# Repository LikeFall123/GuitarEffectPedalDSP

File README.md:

BME Schönhhertz SEM Guitar Pedal Project

Addig digital effects to the sound of the guitar, by processing it with an STM32 microcontroller and a CODEC.

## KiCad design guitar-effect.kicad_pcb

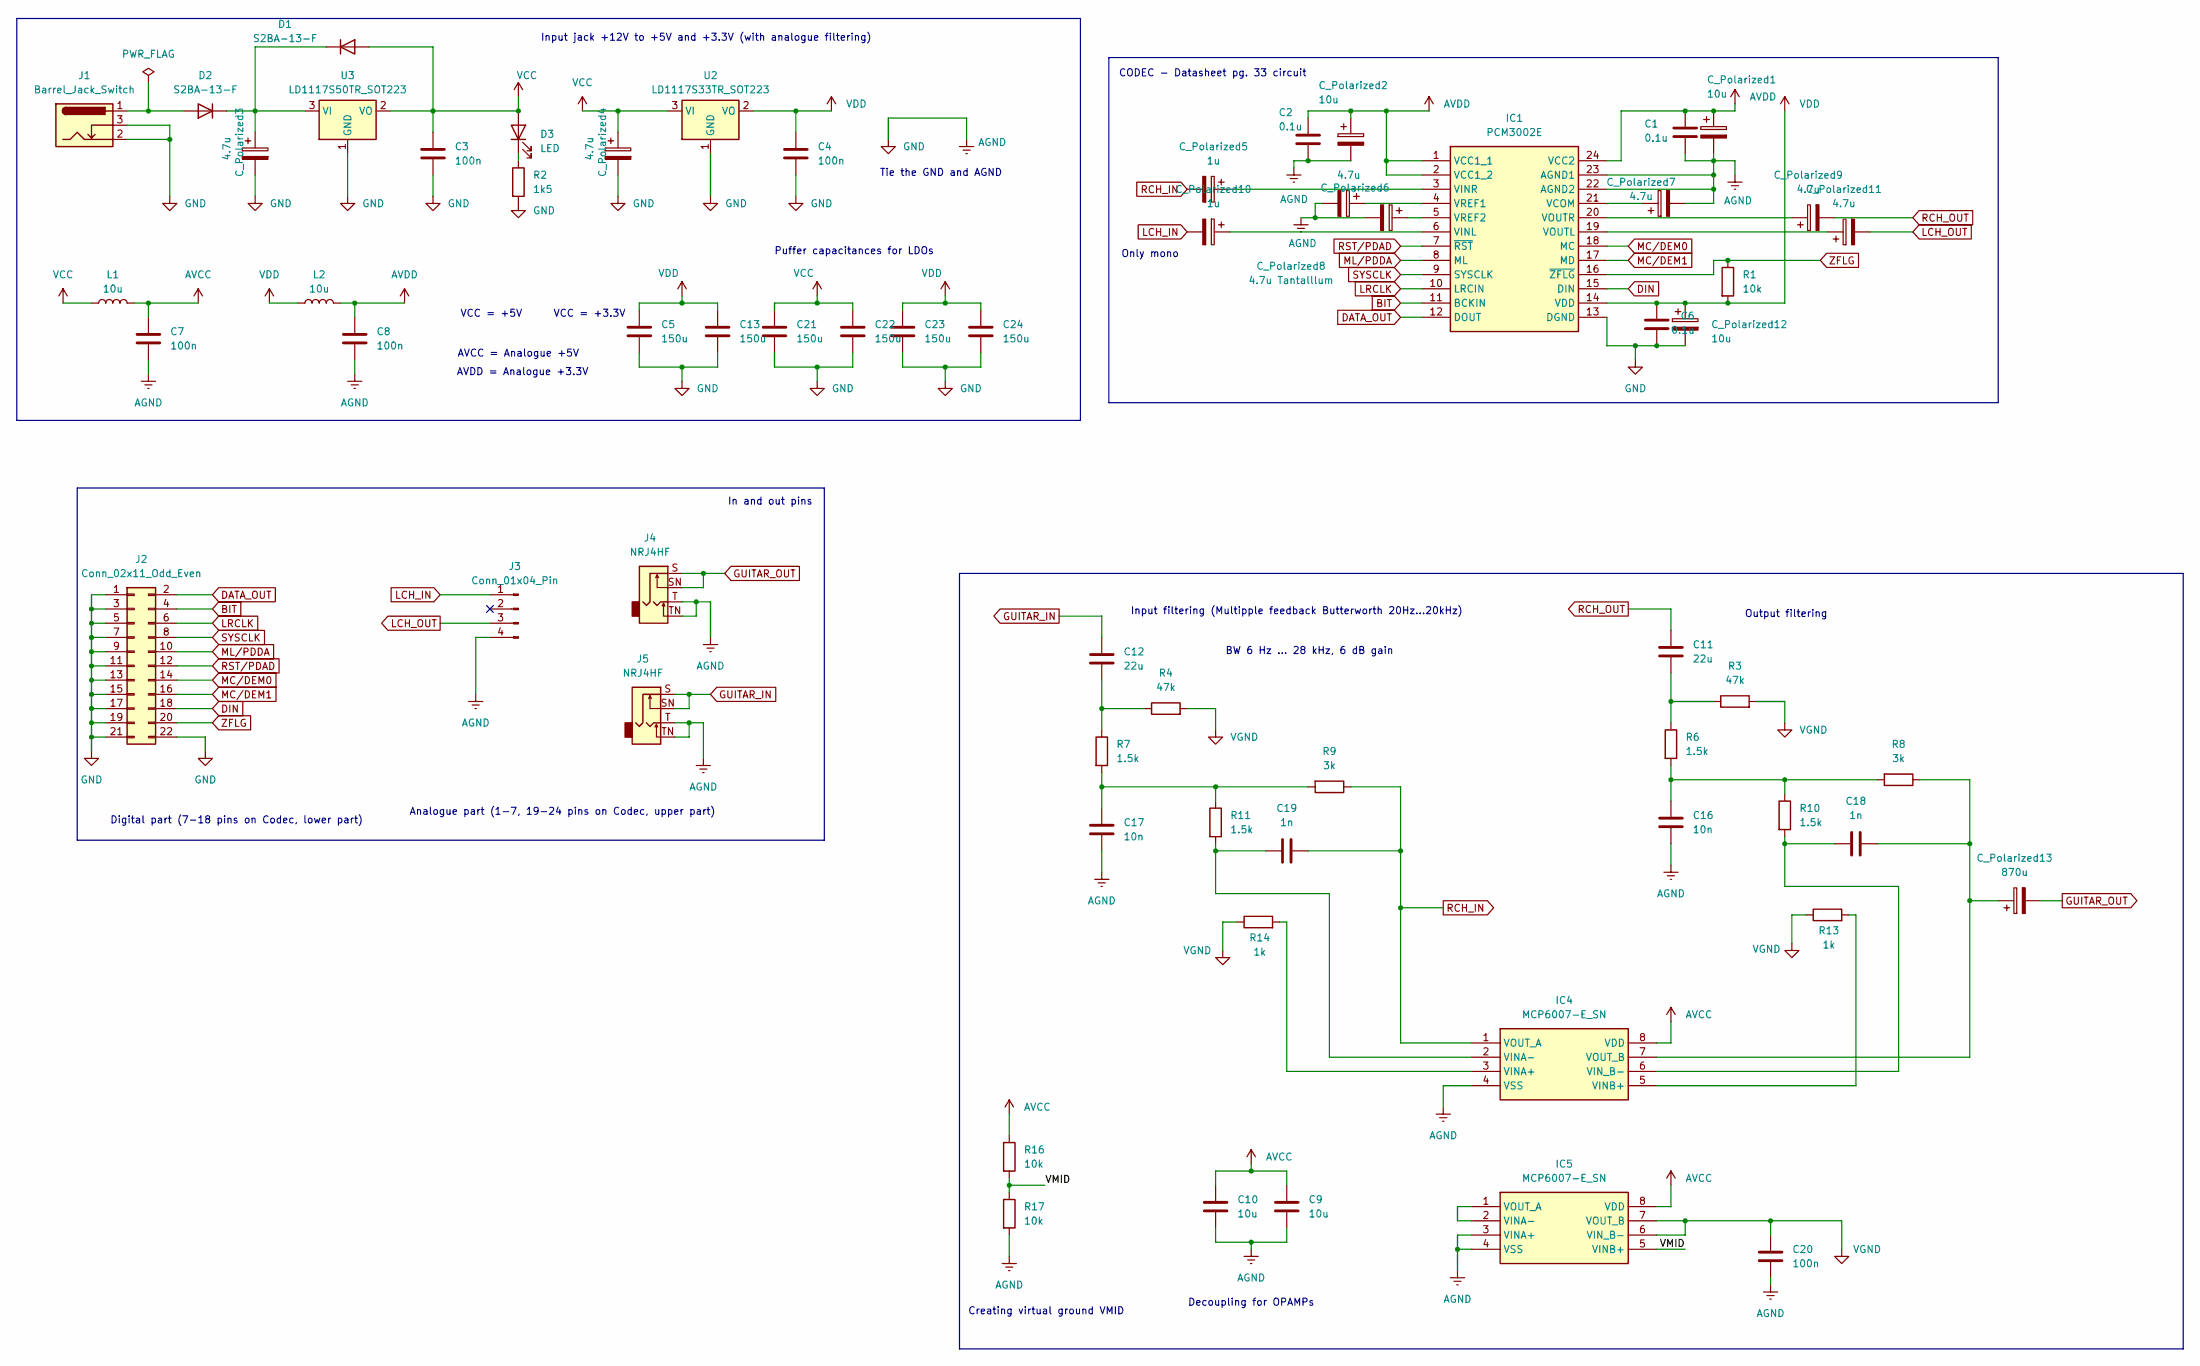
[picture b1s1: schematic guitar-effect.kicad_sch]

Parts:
C1, C2, C6: 0.1u; C_0805_2012Metric
C3, C4, C7, C8, C20: 100n; C_0805_2012Metric
C5, C13, C21, C22, C23, C24: 150u; C_1206_3216Metric
C9, C10: 10u; C_1206_3216Metric
C11, C12: 22u; C_0805_2012Metric
C16, C17: 10n; C_0805_2012Metric
C18, C19: 1n; C_0805_2012Metric
C_Polarized1, C_Polarized2, C_Polarized12: 10u; CP_Radial_D4.0mm_P1.50mm
C_Polarized3, C_Polarized4, C_Polarized6, C_Polarized7, C_Polarized9, C_Polarized11: 4.7u; CP_Radial_D4.0mm_P1.50mm
C_Polarized5, C_Polarized10: 1u; CP_Radial_D4.0mm_P1.50mm
C_Polarized8: 4.7u Tantalllum; CP_Radial_D4.0mm_P1.50mm
C_Polarized13: 870u; CP_Radial_D4.0mm_P1.50mm
D1, D2: S2BA-13-F; D_SMA
D3: LED; LED_0805_2012Metric_Pad1.15x1.40mm_HandSolder
IC1: PCM3002E; SOP65P780X200-24N; Mouser Part Number 595-PCM3002E
IC4, IC5: MCP6007-E_SN; SOIC127P600X175-8N; Mouser Part Number 579-MCP6007-E/SN
J1: Barrel_Jack_Switch; BarrelJack_Horizontal
J2: Conn_02x11_Odd_Even; PinHeader_2x11_P2.54mm_Vertical
J3: Conn_01x04_Pin; PinHeader_1x04_P2.54mm_Vertical
J4, J5: NRJ4HF; Jack_6.35mm_Neutrik_NRJ4HF_Horizontal
L1, L2: 10u; L_0805_2012Metric_Pad1.15x1.40mm_HandSolder
R1, R16, R17: 10k; R_0805_2012Metric
R2: 1k5; R_0805_2012Metric_Pad1.20x1.40mm_HandSolder
R3, R4: 47k; R_0805_2012Metric
R6, R7, R10, R11: 1.5k; R_0805_2012Metric
R8, R9: 3k; R_0805_2012Metric
R13, R14: 1k; R_0805_2012Metric
U2: LD1117S33TR_SOT223; SOT-223-3_TabPin2
U3: LD1117S50TR_SOT223; SOT-223-3_TabPin2

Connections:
/VMID: IC5.5 (VINB+), R16.2, R17.1
AGND: C1.2, C2.2, C3.2, C4.2, C5.2, C6.2, C7.2, C8.2, C9.2, C10.2, C13.2, C16.1, C17.1, C20.2, C21.2, C22.2, C23.2, C24.2, C_Polarized1.2, C_Polarized2.2, C_Polarized3.2, C_Polarized4.2, C_Polarized6.2, C_Polarized7.2, C_Polarized8.2, C_Polarized12.2, IC1.13 (DGND), IC1.22 (AGND2), IC1.23 (AGND1), IC4.4 (VSS), IC5.3 (VINA+), IC5.4 (VSS), J1.2, J1.3, J2.1, J2.3, J2.5, J2.7, J2.9, J2.11, J2.13, J2.15, J2.17, J2.19, J2.21, J2.22, J3.4, J4.T, J4.TN, J5.T, J5.TN, R2.2, R17.2, U2.1 (GND), U3.1 (GND)
AVCC: C7.1, C9.1, C10.1, IC4.8 (VDD), IC5.8 (VDD), L1.2, R16.1
AVDD: C1.1, C2.1, C8.1, C_Polarized1.1, C_Polarized2.1, IC1.1 (VCC1_1), IC1.2 (VCC1_2), IC1.24 (VCC2), L2.2
BIT: IC1.11 (BCKIN), J2.4
DATA_OUT: IC1.12 (DOUT), J2.2
DIN: IC1.15 (DIN), J2.18
GUITAR_IN: C12.2, J5.S, J5.SN
GUITAR_OUT: C_Polarized13.2, J4.S, J4.SN
LCH_IN: C_Polarized10.2, J3.1
LCH_OUT: C_Polarized11.2, J3.3
LRCLK: IC1.10 (LRCIN), J2.6
MC/DEM0: IC1.18 (MC), J2.14
MC/DEM1: IC1.17 (MD), J2.16
ML/PDDA: IC1.8 (ML), J2.10
unnamed: C11.1, R3.1, R6.1
unnamed: C12.1, R4.1, R7.1
unnamed: C16.2, R6.2, R8.2, R10.1
unnamed: C17.2, R7.2, R9.2, R11.1
unnamed: C_Polarized3.1, D1.1 (K), D2.1 (K), U3.3 (VI)
unnamed: D2.2 (A), J1.1
unnamed: D3.1 (K), R2.1
unnamed: C_Polarized7.1, IC1.21 (VCOM)
unnamed: C_Polarized10.1, IC1.6 (VINL)
unnamed: C_Polarized5.1, IC1.3 (VINR)
unnamed: C_Polarized11.1, IC1.19 (VOUTL)
unnamed: C_Polarized9.1, IC1.20 (VOUTR)
unnamed: C_Polarized6.1, IC1.4 (VREF1)
unnamed: C_Polarized8.1, IC1.5 (VREF2)
unnamed: IC4.3 (VINA+), R14.2
unnamed: C19.1, IC4.2 (VINA-), R11.2
unnamed: IC4.5 (VINB+), R13.2
unnamed: C18.1, IC4.6 (VIN_B-), R10.2
unnamed: C18.2, C_Polarized13.1, IC4.7 (VOUT_B), R8.1
unnamed: IC5.1 (VOUT_A), IC5.2 (VINA-)
RCH_IN: C19.2, C_Polarized5.2, IC4.1 (VOUT_A), R9.1
RCH_OUT: C11.2, C_Polarized9.2
RST/PDAD: IC1.7 (~RST), J2.12
SYSCLK: IC1.9 (SYSCLK), J2.8
VCC: C3.1, C21.1, C22.1, C_Polarized4.1, D1.2 (A), D3.2 (A), L1.1, U2.3 (VI), U3.2 (VO)
VDD: C4.1, C5.1, C6.1, C13.1, C23.1, C24.1, C_Polarized12.1, IC1.14 (VDD), L2.1, R1.2, U2.2 (VO)
VGND: C20.1, IC5.6 (VIN_B-), IC5.7 (VOUT_B), R3.2, R4.2, R13.1, R14.1
ZFLG: IC1.16 (~ZFLG), J2.20, R1.1

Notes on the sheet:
BW 6 Hz ... 28 kHz, 6 dB gain
Output filtering
AVDD = Analogue +3.3V
Input filtering (Multipple feedback Butterworth 20Hz...20kHz)
In and out pins
Digital part (7-18 pins on Codec, lower part)
VCC = +5V
Tie the GND and AGND
VCC = +3.3V
AVCC = Analogue +5V
Only mono
Creating virtual ground VMID
Input jack +12V to +5V and +3.3V (with analogue filtering)
Analogue part (1-7, 19-24 pins on Codec, upper part)
CODEC - Datasheet pg. 33 circuit
Decoupling for OPAMPs
Puffer capacitances for LDOs

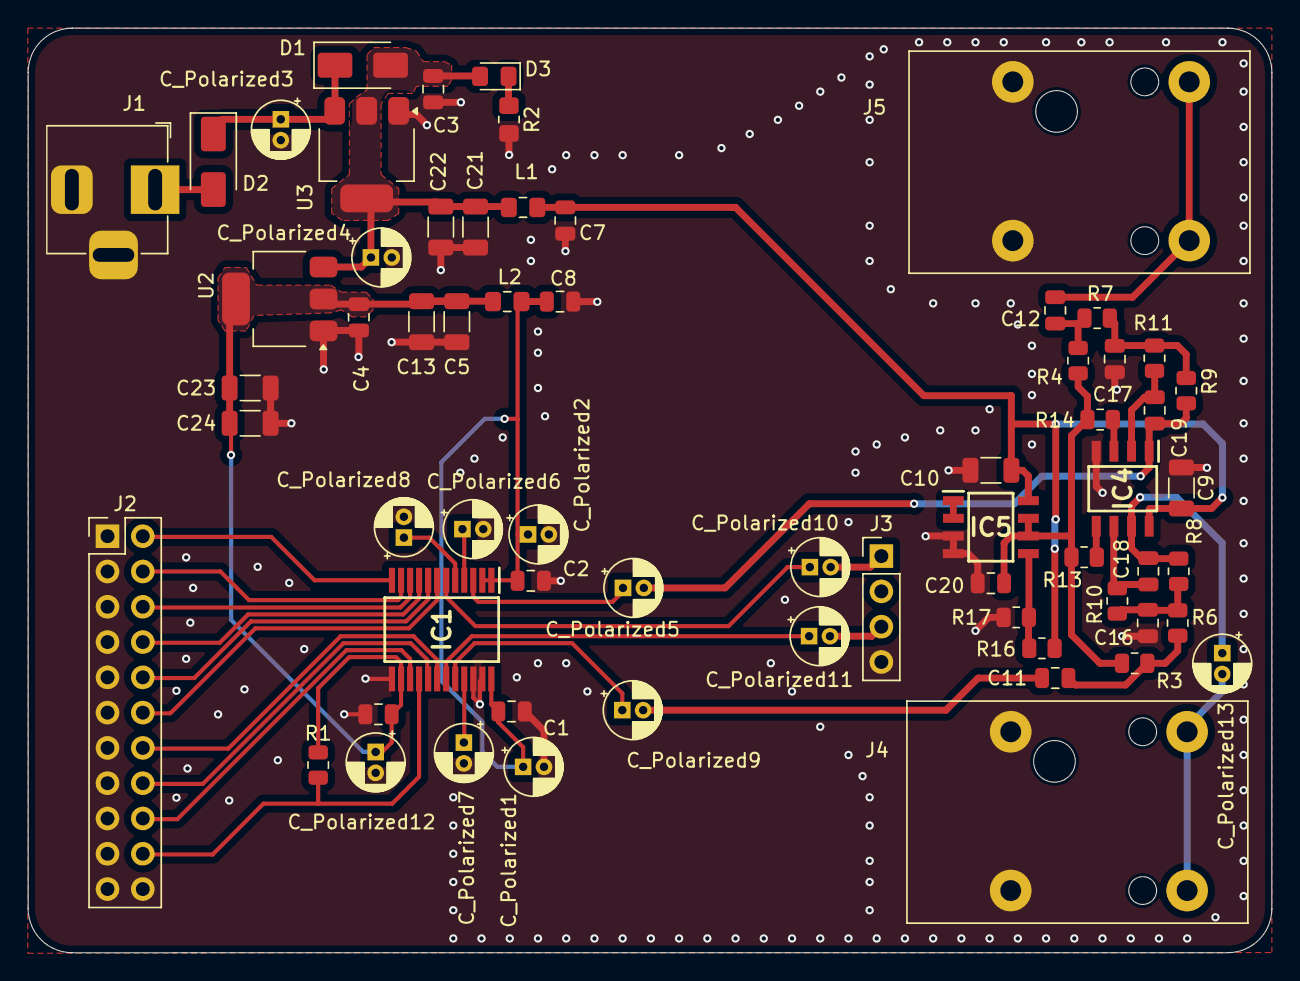
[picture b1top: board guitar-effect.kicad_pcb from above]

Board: 2 copper layers, 89.5 x 66.6 mm, 64 parts (0 on the bottom side), 43 nets.

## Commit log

2024-06-12 Add files via upload
    Voltage regulators
2024-09-30 PCB design
    Power supply withs LDOs added to schematic. V1.0 PCB design. Gerber and drill files
2024-10-04 PCB v1.2
    Connecting the digital and analogue ground. Analogue parts are put farther away from the digital parts, on the right side of the PCB.
2024-10-26 Forrasztáshoz
